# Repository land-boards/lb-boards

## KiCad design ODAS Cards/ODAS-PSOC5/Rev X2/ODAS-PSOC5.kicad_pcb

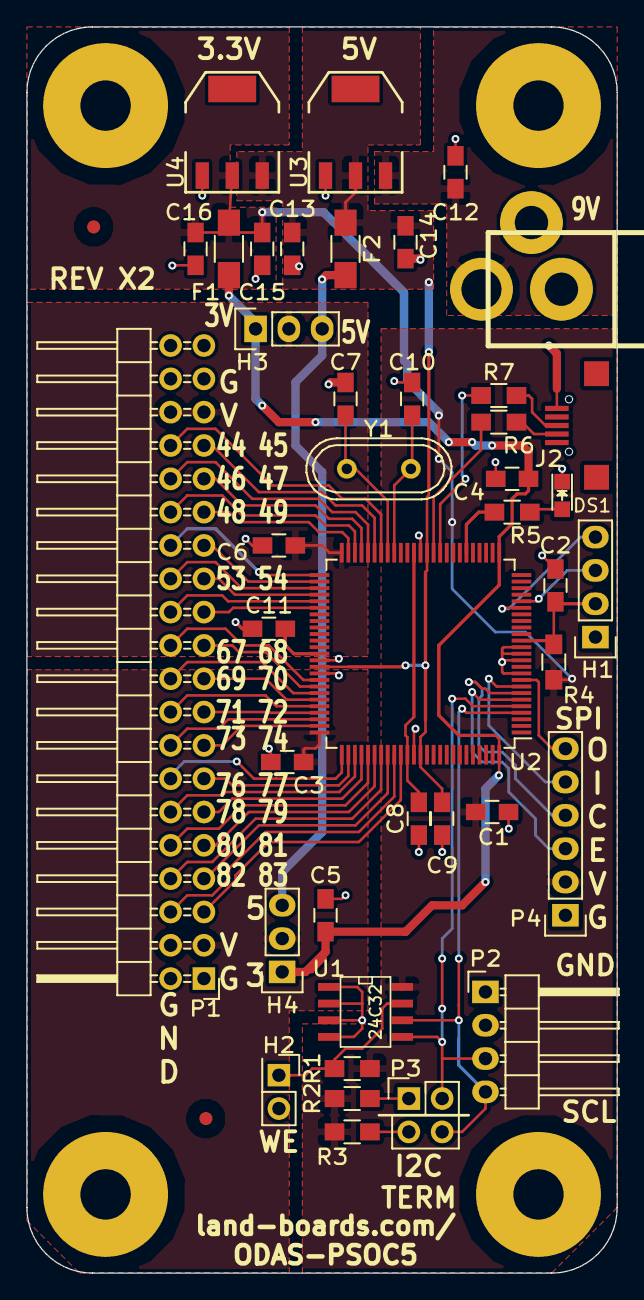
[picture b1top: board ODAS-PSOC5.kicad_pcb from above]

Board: 2 copper layers, 45.0 x 95.0 mm, 48 parts (1 on the bottom side), 60 nets.

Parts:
C1, C2, C3, C4, C5, C6, C9, C12, C13, C14, C15, C16: 0.1uF; C_0805_HandSoldering
C7, C10: C; C_0805_HandSoldering
C8, C11: 1uF; C_0805_HandSoldering
DS1: LED-fixed; LED_0805
F1, F2: FUSE; R_1206_HandSoldering
FID1, FID2: CONN_1; FIDUCIAL
H1: CONN_01X04; Pin_Header_Straight_1x04
H2: CONN_2; Pin_Header_Straight_2x01
H3, H4: CONN_01X03; Pin_Header_Straight_1x03
J1: DCJ0202; JACK_3.5MM
J2: USB-MICRO-B; USB_Micro-B-Wellco-SMT
MTG1, MTG2, MTG3, MTG4: CONN_1; MTG-6-32
P1: CONN_01X40; Pin_Header_Angled_2x20
P2: CONN_01X04; Pin_Header_Angled_1x04
P3: CONN_02X02; Pin_Header_Straight_2x02
P4: CONN_01X06; Pin_Header_Straight_1x06
R1: 1K; R_0805_HandSoldering
R2, R3, R4: 3.9K; R_0805_HandSoldering
R5: 120; R_0805_HandSoldering
R6, R7: 22; R_0805_HandSoldering
TEST: COUPON; REV_BLOCK
U1: 24C32; SO8E-wider
U2: CY8C5267AXI-LP051; TQFP-100_14x14mm_Pitch0.5mm
U3, U4: AP1117; SOT223
Y1: Crystal_Small; Crystal_HC49-U_Vertical

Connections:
+3.3VP: C4.1, C5.1, F1.1, H3.1, H4.1, U2.26, U2.100
+3V3: C1.1, C15.1, C16.1, F1.2, P2.2, P4.2, R1.1, R2.2, R3.2, R4.2, U1.8, U4.2
+5V: C9.2, C13.1, C14.1, F2.2, U2.37, U2.65, U2.88, U3.2, U4.3
+5VP: F2.1, H3.3, H4.3
/+9V: C12.1, J1.1, U3.3
/IO_22: C2.1, H1.2, R4.1, U2.15
/IO_23: H1.3, U2.21
/IO_24: H1.4, U2.20
/P5-4: R5.1, U2.31
/P44: P1.34, U2.44
/P45: P1.33, U2.45
/P46: P1.32, U2.46
/P47: P1.31, U2.47
/P48: P1.30, U2.48
/P49: P1.29, U2.49
/P51: P1.28, U2.51
/P52: P1.27, U2.52
/P53: P1.26, U2.53
/P54: P1.25, U2.54
/P55: P1.24, U2.55
/P56: P1.23, U2.56
/P67: P1.22, U2.67
/P68: P1.21, U2.68
/P69: P1.20, U2.69
/P70: P1.19, U2.70
/P71: P1.18, U2.71
/P72: P1.17, U2.72
/P73: P1.16, U2.73
/P74: P1.15, U2.74
/P76: P1.14, U2.76
/P77: P1.13, U2.77
/P78: P1.12, U2.78
/P79: P1.11, U2.79
/P80: P1.10, U2.80
/P81: P1.9, U2.81
/P82: P1.8, U2.82
/P83: P1.7, U2.83
/P84: P1.6, U2.84
/P85: P1.5, U2.85
/SCL: P2.4, P3.4, U1.6, U2.4
/SDA: P2.3, P3.2, U1.5, U2.5
/SPICE0: P4.3, U2.6
/SPIMISO: P4.5, U2.8
/SPIMOSI: P4.6, U2.9
/SPISCK: P4.4, U2.7
/USB-DM: J2.2, R6.1
/USB-DP: J2.3, R7.1
/VZ0: C3.1, H4.2, P1.3, P1.4, U2.75
/VZ3: C6.1, H3.2, P1.35, P1.36, U2.50
/WR: H2.1, R1.2, U1.7
GND: C1.2, C2.2, C3.2, C4.2, C5.2, C6.2, C7.1, C8.1, C9.1, C10.1, C11.1, C12.2, C13.2, C14.2, C15.2, C16.2, DS1.1, H1.1, H2.2, J1.2, J1.3, J2.5, P1.1, P1.2, P1.37, P1.38, P2.1, P4.1, U1.1, U1.2, U1.3, U1.4, U2.10, U2.12, U2.13, U2.14, U2.38, U2.64, U2.66, U2.87, U3.1, U4.1
unnamed: C7.2, U2.43, Y1.1
unnamed: C8.2, U2.39, U2.86
unnamed: C10.2, U2.42, Y1.2
unnamed: C11.2, U2.63
unnamed: DS1.2, R5.2
unnamed: P3.1, R2.1
unnamed: P3.3, R3.1
unnamed: R6.2, U2.36
unnamed: R7.2, U2.35

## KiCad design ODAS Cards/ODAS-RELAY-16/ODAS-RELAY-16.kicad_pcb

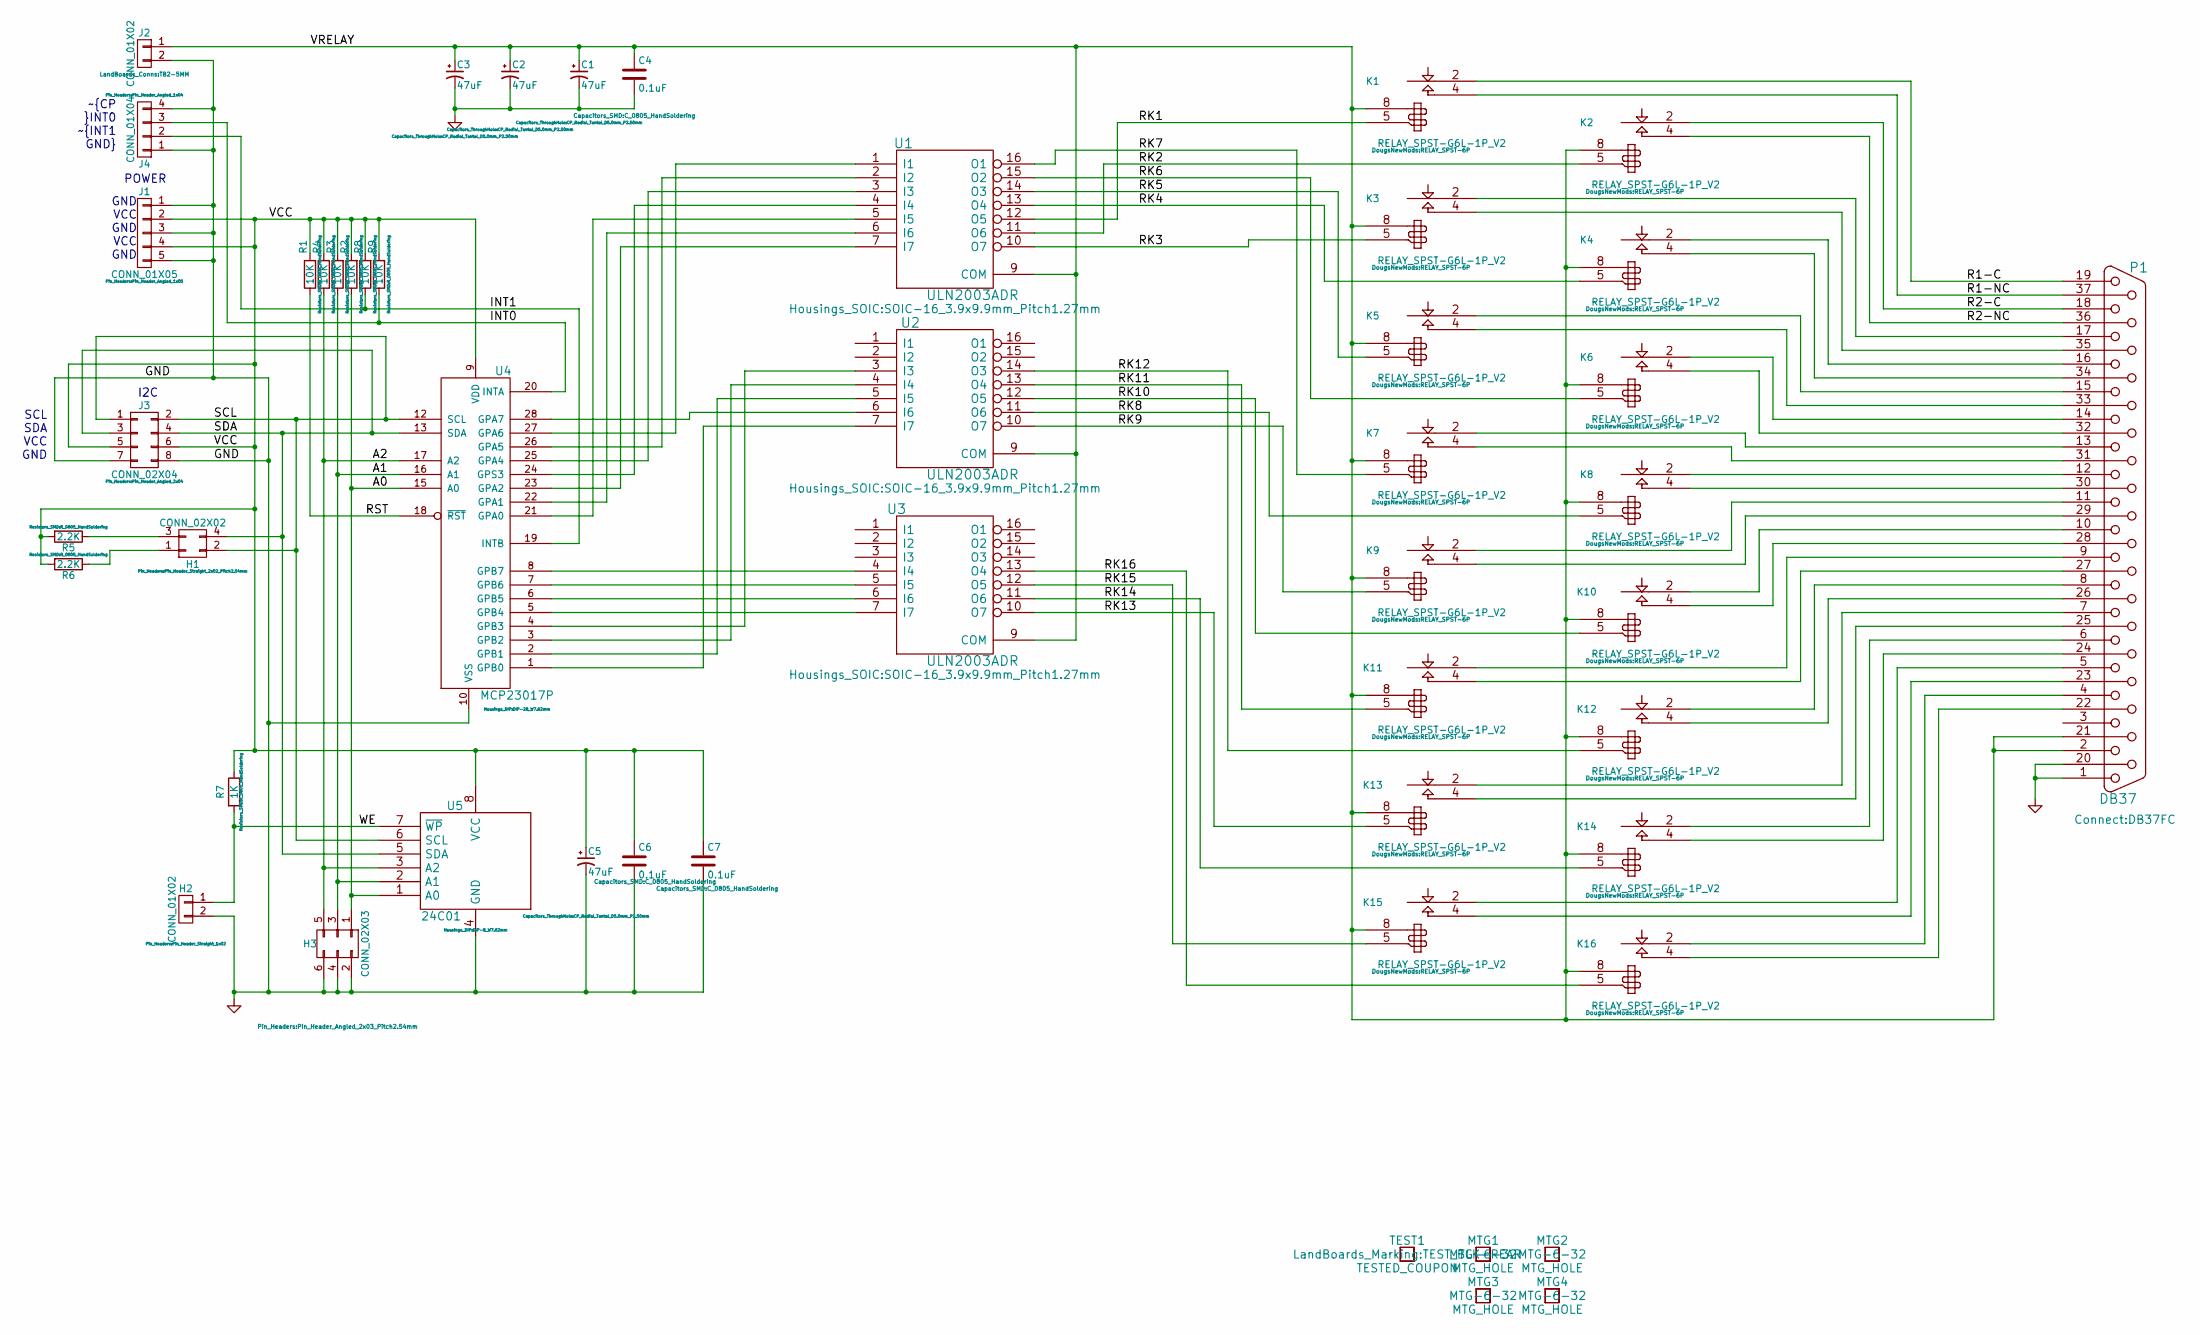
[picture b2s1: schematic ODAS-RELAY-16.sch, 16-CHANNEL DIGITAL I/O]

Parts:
C1, C2, C3, C5: 47uF; CP_Radial_Tantal_D5.0mm_P2.50mm
C4, C6, C7: 0.1uF; C_0805_HandSoldering
H1: CONN_02X02; Pin_Header_Straight_2x02_Pitch2.54mm
H2: CONN_01X02; Pin_Header_Straight_1x02
H3: CONN_02X03; Pin_Header_Angled_2x03_Pitch2.54mm
J1: CONN_01X05; Pin_Header_Angled_1x05
J2: CONN_01X02; TB2-5MM
J3: CONN_02X04; Pin_Header_Angled_2x04
J4: CONN_01X04; Pin_Header_Angled_1x04
K1, K2, K3, K4, K5, K6, K7, K8, K9, K10, K11, K12, K13, K14, K15, K16: RELAY_SPST-G6L-1P_V2; RELAY_SPST-6P
MTG1, MTG2, MTG3, MTG4: MTG_HOLE; MTG-6-32
P1: DB37; DB37FC
R1, R2, R3, R4, R8, R9: 10K; R_0805_HandSoldering
R5, R6: 2.2K; R_0805_HandSoldering
R7: 1K; R_0805_HandSoldering
TEST1: TESTED_COUPON; TEST_BLK-REAR
U1, U2, U3: ULN2003ADR; SOIC-16_3.9x9.9mm_Pitch1.27mm
U4: MCP23017P; DIP-28_W7.62mm
U5: 24C01; DIP-8_W7.62mm

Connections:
/A0: H3.1, R2.1, U4.15 (A0), U5.1 (A0)
/A1: H3.3, R3.1, U4.16 (A1), U5.2 (A1)
/A2: H3.5, R4.1, U4.17 (A2), U5.3 (A2)
/INT0: J4.3, R9.1, U4.20 (INTA)
/INT1: J4.2, R8.1, U4.19 (INTB)
/R1-C: K1.2 (C1), P1.19
/R1-NC: K1.4 (T1), P1.37
/R2-C: K2.2 (C1), P1.18
/R2-NC: K2.4 (T1), P1.36
/RK1: K1.5, U1.12 (O5)
/RK2: K2.5, U1.11 (O6)
/RK3: K3.5, U1.10 (O7)
/RK4: K4.5, U1.13 (O4)
/RK5: K5.5, U1.14 (O3)
/RK6: K6.5, U1.15 (O2)
/RK7: K7.5, U1.16 (O1)
/RK8: K8.5, U2.11 (O6)
/RK9: K9.5, U2.10 (O7)
/RK10: K10.5, U2.12 (O5)
/RK11: K11.5, U2.13 (O4)
/RK12: K12.5, U2.14 (O3)
/RK13: K13.5, U3.10 (O7)
/RK14: K14.5, U3.11 (O6)
/RK15: K15.5, U3.12 (O5)
/RK16: K16.5, U3.13 (O4)
/RST: R1.1, U4.18 (~RST)
/SCL: H1.2, J3.1, J3.2, U4.12 (SCL), U5.6 (SCL)
/SDA: H1.4, J3.3, J3.4, U4.13 (SDA), U5.5 (SDA)
/VCC: C5.1, C6.1, C7.1, J1.2, J1.4, J3.5, J3.6, R1.2, R2.2, R3.2, R4.2, R5.2, R6.2, R7.1, R8.2, R9.2, U4.9 (VDD), U5.8 (VCC)
/VRELAY: C1.1, C2.1, C3.1, C4.1, J2.1, K1.8, K2.8, K3.8, K4.8, K5.8, K6.8, K7.8, K8.8, K9.8, K10.8, K11.8, K12.8, K13.8, K14.8, K15.8, K16.8, P1.2, P1.21, U1.9 (COM), U2.9 (COM), U3.9 (COM)
/WE: H2.1, R7.2, U5.7 (~WP)
GND: C1.2, C2.2, C3.2, C4.2, C5.2, C6.2, C7.2, H2.2, H3.2, H3.4, H3.6, J1.1, J1.3, J1.5, J2.2, J3.7, J3.8, J4.1, J4.4, P1.1, P1.20, U1.8 (GND), U2.8 (GND), U3.8 (GND), U4.10 (VSS), U5.4 (GND)
unnamed: H1.1, R6.1
unnamed: H1.3, R5.1
unnamed: K3.2 (C1), P1.17
unnamed: K3.4 (T1), P1.35
unnamed: K4.2 (C1), P1.16
unnamed: K4.4 (T1), P1.34
unnamed: K5.2 (C1), P1.15
unnamed: K5.4 (T1), P1.33
unnamed: K6.2 (C1), P1.14
unnamed: K6.4 (T1), P1.32
unnamed: K7.2 (C1), P1.13
unnamed: K7.4 (T1), P1.31
unnamed: K8.2 (C1), P1.12
unnamed: K8.4 (T1), P1.30
unnamed: K9.2 (C1), P1.11
unnamed: K9.4 (T1), P1.29
unnamed: K10.2 (C1), P1.10
unnamed: K10.4 (T1), P1.28
unnamed: K11.2 (C1), P1.9
unnamed: K11.4 (T1), P1.27
unnamed: K12.2 (C1), P1.8
unnamed: K12.4 (T1), P1.26
unnamed: K13.2 (C1), P1.7
unnamed: K13.4 (T1), P1.25
unnamed: K14.2 (C1), P1.6
unnamed: K14.4 (T1), P1.24
unnamed: K15.2 (C1), P1.5
unnamed: K15.4 (T1), P1.23
unnamed: K16.2 (C1), P1.4
unnamed: K16.4 (T1), P1.22
unnamed: U1.1 (I1), U4.27 (GPA6)
unnamed: U1.2 (I2), U4.26 (GPA5)
unnamed: U1.3 (I3), U4.25 (GPA4)
unnamed: U1.4 (I4), U4.24 (GPS3)
unnamed: U1.5 (I5), U4.21 (GPA0)
unnamed: U1.6 (I6), U4.22 (GPA1)
unnamed: U1.7 (I7), U4.23 (GPA2)
unnamed: U2.3 (I3), U4.4 (GPB3)
unnamed: U2.4 (I4), U4.3 (GPB2)
unnamed: U2.5 (I5), U4.2 (GPB1)
unnamed: U2.6 (I6), U4.28 (GPA7)
unnamed: U2.7 (I7), U4.1 (GPB0)
unnamed: U3.4 (I4), U4.8 (GPB7)
unnamed: U3.5 (I5), U4.7 (GPB6)
unnamed: U3.6 (I6), U4.6 (GPB5)
unnamed: U3.7 (I7), U4.5 (GPB4)

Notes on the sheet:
SCL SDA VCC GND
GND VCC GND VCC GND
~CP ~INT0 ~INT1 GND
POWER
I2C

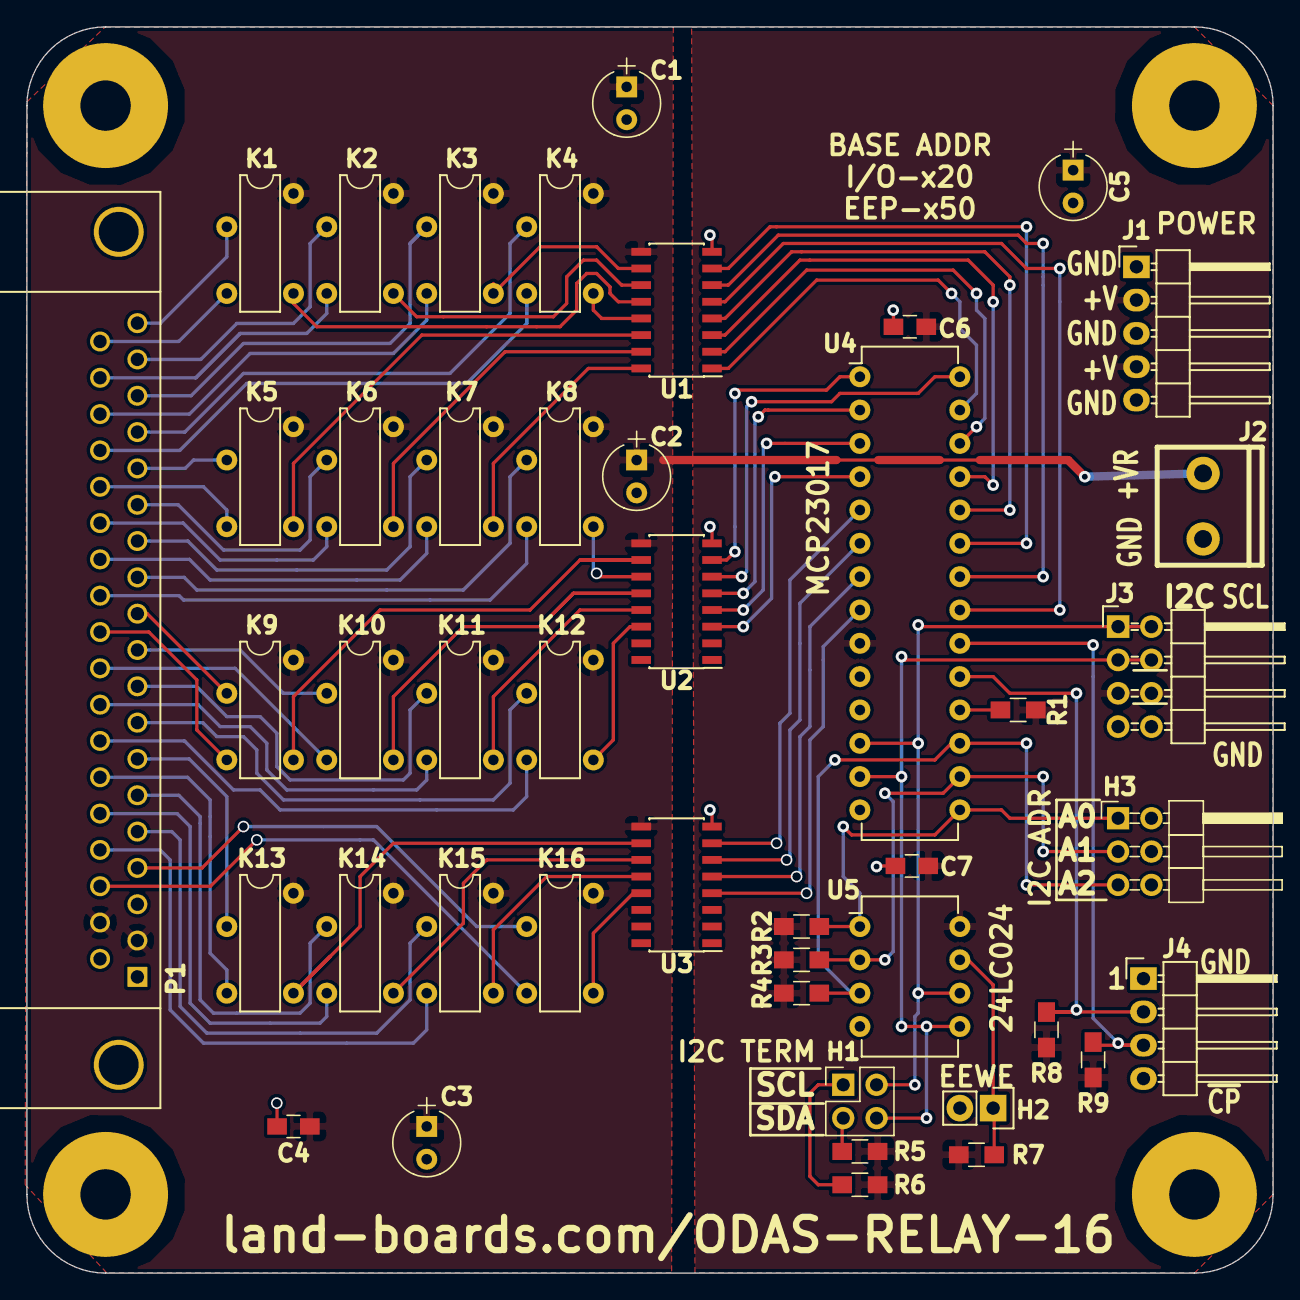
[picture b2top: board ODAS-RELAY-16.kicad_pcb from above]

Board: 2 copper layers, 95.0 x 95.0 mm, 50 parts (0 on the bottom side), 78 nets.

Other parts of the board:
TEST: TESTED_COUPON; TEST_BLK-REAR

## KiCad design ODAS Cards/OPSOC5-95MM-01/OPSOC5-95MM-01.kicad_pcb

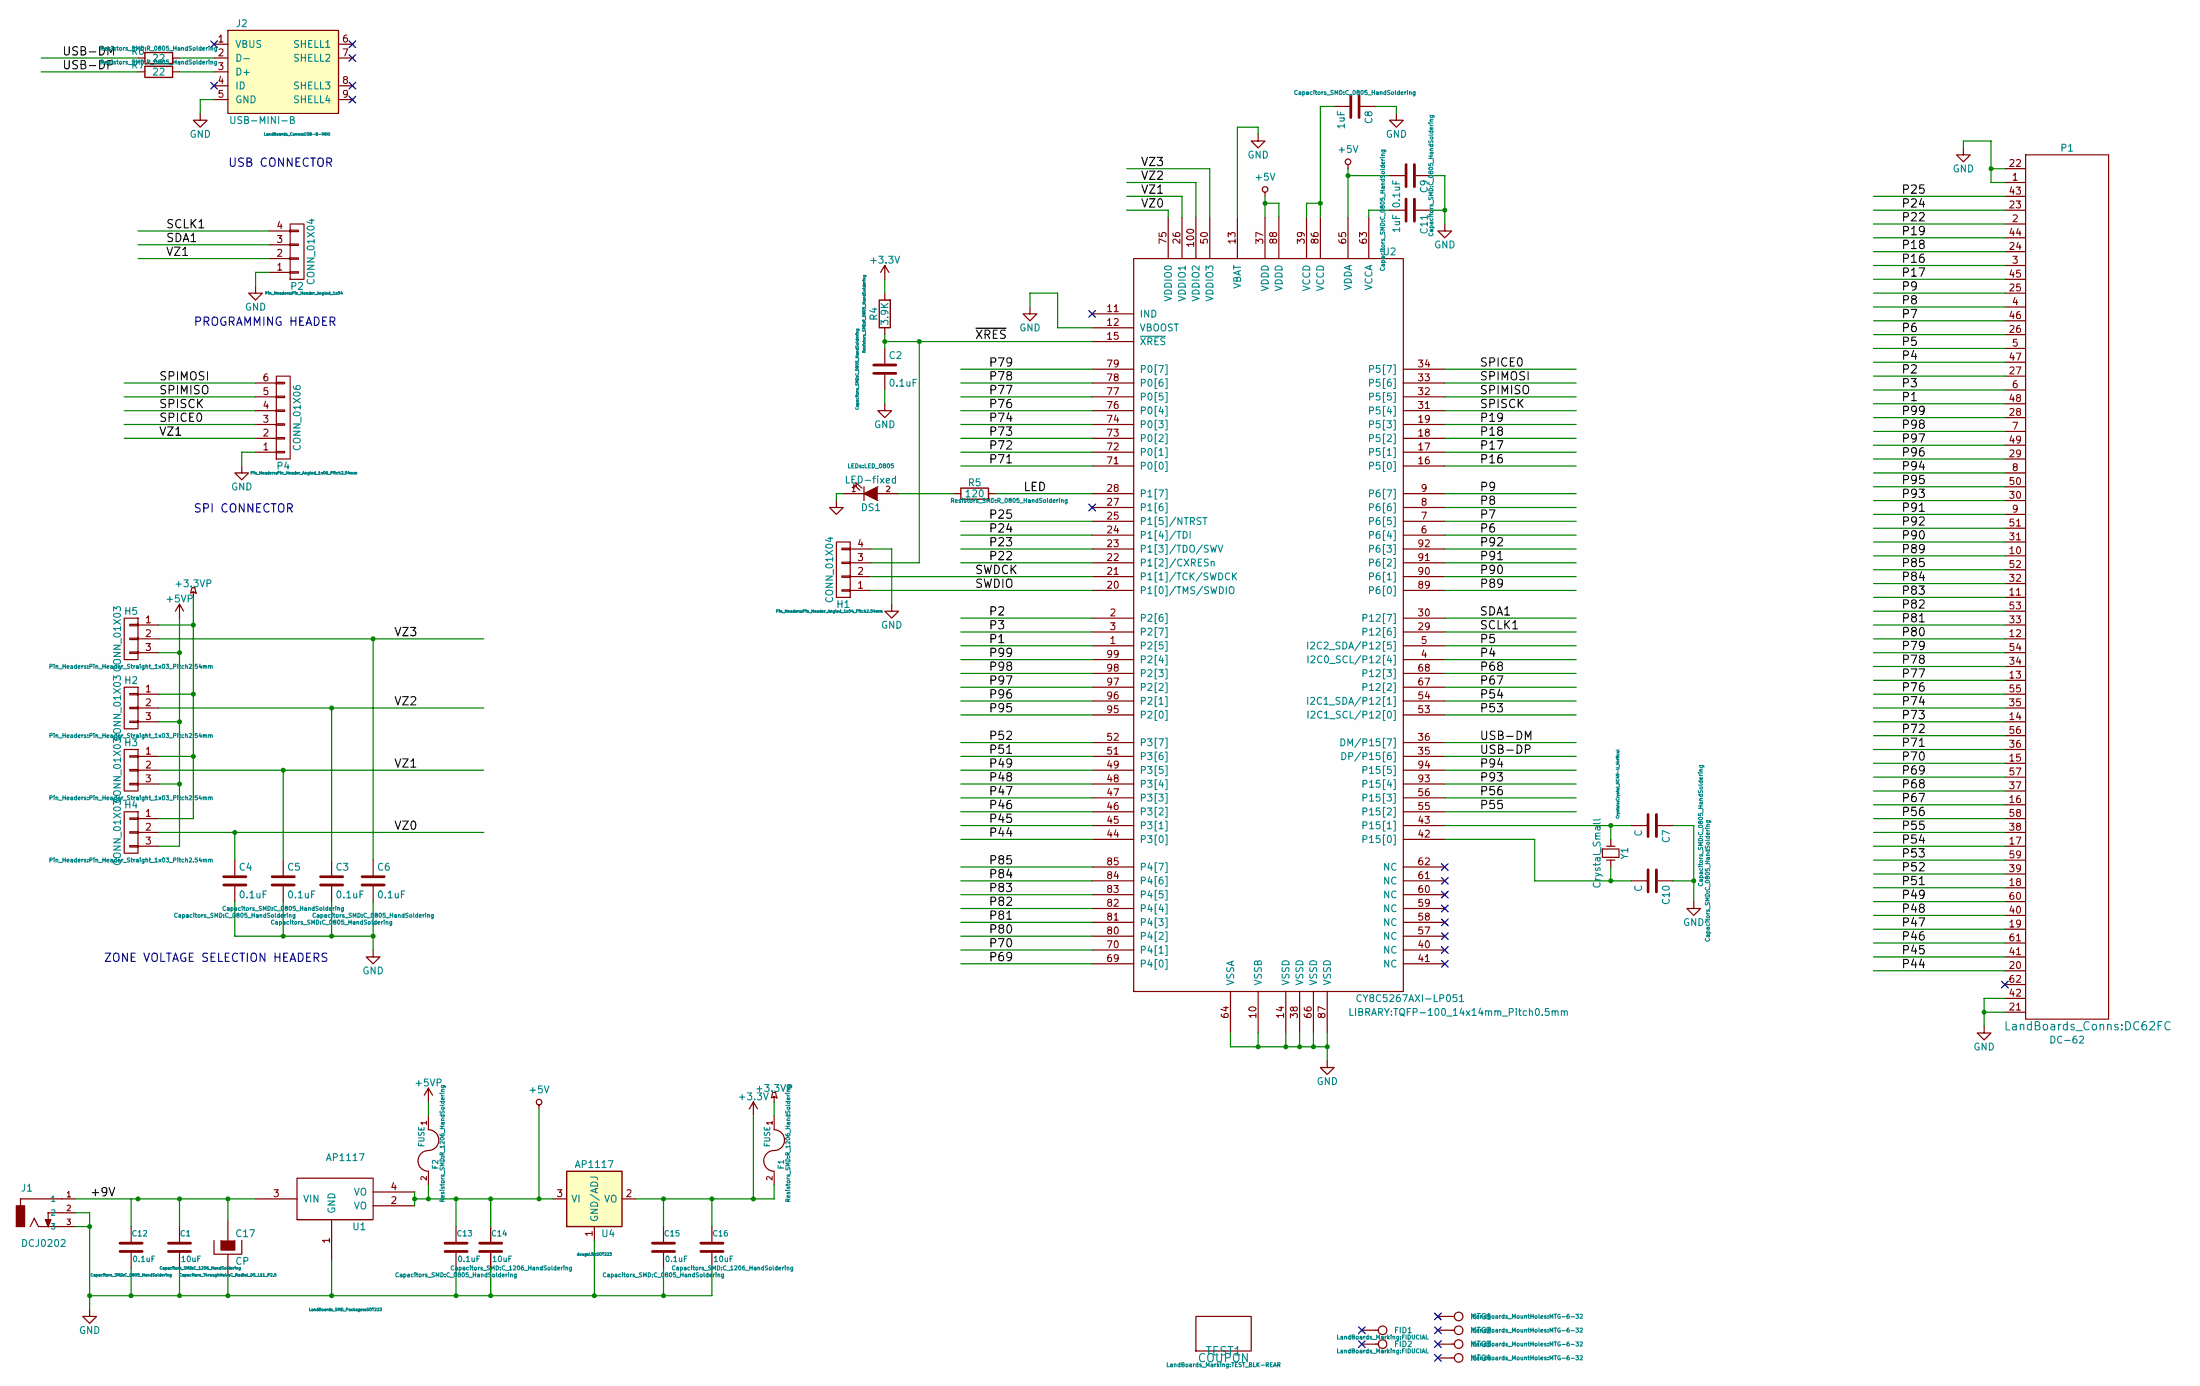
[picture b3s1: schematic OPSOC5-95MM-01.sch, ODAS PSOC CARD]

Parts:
C1, C14, C16: 10uF; C_1206_HandSoldering
C2, C3, C4, C5, C6, C9, C12, C13, C15: 0.1uF; C_0805_HandSoldering
C7, C10: C; C_0805_HandSoldering
C8, C11: 1uF; C_0805_HandSoldering
C17: CP; C_Radial_D5_L11_P2.5
DS1: LED-fixed; LED_0805
F1, F2: FUSE; R_1206_HandSoldering
FID1, FID2: CONN_1; FIDUCIAL
H1: CONN_01X04; Pin_Header_Angled_1x04_Pitch2.54mm
H2, H3, H4, H5: CONN_01X03; Pin_Header_Straight_1x03_Pitch2.54mm
J1: DCJ0202; JACK_3.5MM
J2: USB-MINI-B; USB-B-MINI
MTG1, MTG2, MTG3, MTG4: CONN_1; MTG-6-32
P1: DC-62; DC62FC
P2: CONN_01X04; Pin_Header_Angled_1x04
P4: CONN_01X06; Pin_Header_Angled_1x06_Pitch2.54mm
R4: 3.9K; R_0805_HandSoldering
R5: 120; R_0805_HandSoldering
R6, R7: 22; R_0805_HandSoldering
TEST1: COUPON; TEST_BLK-REAR
U1, U4: AP1117; SOT223
U2: CY8C5267AXI-LP051; TQFP-100_14x14mm_Pitch0.5mm
Y1: Crystal_Small; Crystal_HC49-U_Vertical

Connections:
+3.3VP: F1.1, H2.1, H3.1, H4.1, H5.1
+3V3: C15.1, C16.1, F1.2, R4.2, U4.2 (VO)
+5V: C9.2, C13.1, C14.1, F2.2, U1.2 (VO), U1.4 (VO), U2.37 (VDDD), U2.65 (VDDA), U2.88 (VDDD), U4.3 (VI)
+5VP: F2.1, H2.3, H3.3, H4.3, H5.3
/+9V: C1.1, C17.1, J1.1, U1.3 (VIN)
/LED: R5.2, U2.28 (P1[7])
/P1: P1.48, U2.1 (P2[5])
/P2: P1.27, U2.2 (P2[6])
/P3: P1.6, U2.3 (P2[7])
/P4: P1.47, U2.4 (I2C0_SCL/P12[4])
/P5: P1.5, U2.5 (I2C2_SDA/P12[5])
/P6: P1.26, U2.6 (P6[4])
/P7: P1.46, U2.7 (P6[5])
/P8: P1.4, U2.8 (P6[6])
/P9: P1.25, U2.9 (P6[7])
/P16: P1.3, U2.16 (P5[0])
/P17: P1.45, U2.17 (P5[1])
/P18: P1.24, U2.18 (P5[2])
/P19: P1.44, U2.19 (P5[3])
/P22: P1.2, U2.22 (P1[2]/CXRESn)
/P24: P1.23, U2.24 (P1[4]/TDI)
/P25: P1.43, U2.25 (P1[5]/NTRST)
/P44: P1.20, U2.44 (P3[0])
/P45: P1.41, U2.45 (P3[1])
/P46: P1.61, U2.46 (P3[2])
/P47: P1.19, U2.47 (P3[3])
/P48: P1.40, U2.48 (P3[4])
/P49: P1.60, U2.49 (P3[5])
/P51: P1.18, U2.51 (P3[6])
/P52: P1.39, U2.52 (P3[7])
/P53: P1.59, U2.53 (I2C1_SCL/P12[0])
/P54: P1.17, U2.54 (I2C1_SDA/P12[1])
/P55: P1.38, U2.55 (P15[2])
/P56: P1.58, U2.56 (P15[3])
/P67: P1.16, U2.67 (P12[2])
/P68: P1.37, U2.68 (P12[3])
/P69: P1.57, U2.69 (P4[0])
/P70: P1.15, U2.70 (P4[1])
/P71: P1.36, U2.71 (P0[0])
/P72: P1.56, U2.72 (P0[1])
/P73: P1.14, U2.73 (P0[2])
/P74: P1.35, U2.74 (P0[3])
/P76: P1.55, U2.76 (P0[4])
/P77: P1.13, U2.77 (P0[5])
/P78: P1.34, U2.78 (P0[6])
/P79: P1.54, U2.79 (P0[7])
/P80: P1.12, U2.80 (P4[2])
/P81: P1.33, U2.81 (P4[3])
/P82: P1.53, U2.82 (P4[4])
/P83: P1.11, U2.83 (P4[5])
/P84: P1.32, U2.84 (P4[6])
/P85: P1.52, U2.85 (P4[7])
/P89: P1.10, U2.89 (P6[0])
/P90: P1.31, U2.90 (P6[1])
/P91: P1.9, U2.91 (P6[2])
/P92: P1.51, U2.92 (P6[3])
/P93: P1.30, U2.93 (P15[4])
/P94: P1.8, U2.94 (P15[5])
/P95: P1.50, U2.95 (P2[0])
/P96: P1.29, U2.96 (P2[1])
/P97: P1.49, U2.97 (P2[2])
/P98: P1.7, U2.98 (P2[3])
/P99: P1.28, U2.99 (P2[4])
/SCLK1: P2.4, U2.29 (P12[6])
/SDA1: P2.3, U2.30 (P12[7])
/SPICE0: P4.3, U2.34 (P5[7])
/SPIMISO: P4.5, U2.32 (P5[5])
/SPIMOSI: P4.6, U2.33 (P5[6])
/SPISCK: P4.4, U2.31 (P5[4])
/SWDCK: H1.2, U2.21 (P1[1]/TCK/SWDCK)
/SWDIO: H1.1, U2.20 (P1[0]/TMS/SWDIO)
/USB-DM: R6.2, U2.36 (DM/P15[7])
/USB-DP: R7.2, U2.35 (DP/P15[6])
/VZ0: C4.1, H4.2, U2.75 (VDDIO0)
/VZ1: C5.1, H3.2, P2.2, P4.2, U2.26 (VDDIO1)
/VZ2: C3.1, H2.2, U2.100 (VDDIO2)
/VZ3: C6.1, H5.2, U2.50 (VDDIO3)
/~XRES: C2.1, H1.3, R4.1, U2.15 (~XRES)
GND: C1.2, C2.2, C3.2, C4.2, C5.2, C6.2, C7.1, C8.1, C9.1, C10.1, C11.1, C12.2, C13.2, C14.2, C15.2, C16.2, C17.2, DS1.1 (K), H1.4, J1.2, J1.3, J2.5 (GND), P1.1, P1.21, P1.22, P1.42, P2.1, P4.1, U1.1 (GND), U2.10 (VSSB), U2.12 (VBOOST), U2.13 (VBAT), U2.14 (VSSD), U2.38 (VSSD), U2.64 (VSSA), U2.66 (VSSD), U2.87 (VSSD), U4.1 (GND/ADJ)
unnamed: C7.2, U2.43 (P15[1]), Y1.1
unnamed: C8.2, U2.39 (VCCD), U2.86 (VCCD)
unnamed: C10.2, U2.42 (P15[0]), Y1.2
unnamed: C11.2, U2.63 (VCCA)
unnamed: DS1.2 (A), R5.1
unnamed: J2.2 (D-), R6.1
unnamed: J2.3 (D+), R7.1

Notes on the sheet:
PROGRAMMING HEADER
USB CONNECTOR
SPI CONNECTOR
ZONE VOLTAGE SELECTION HEADERS

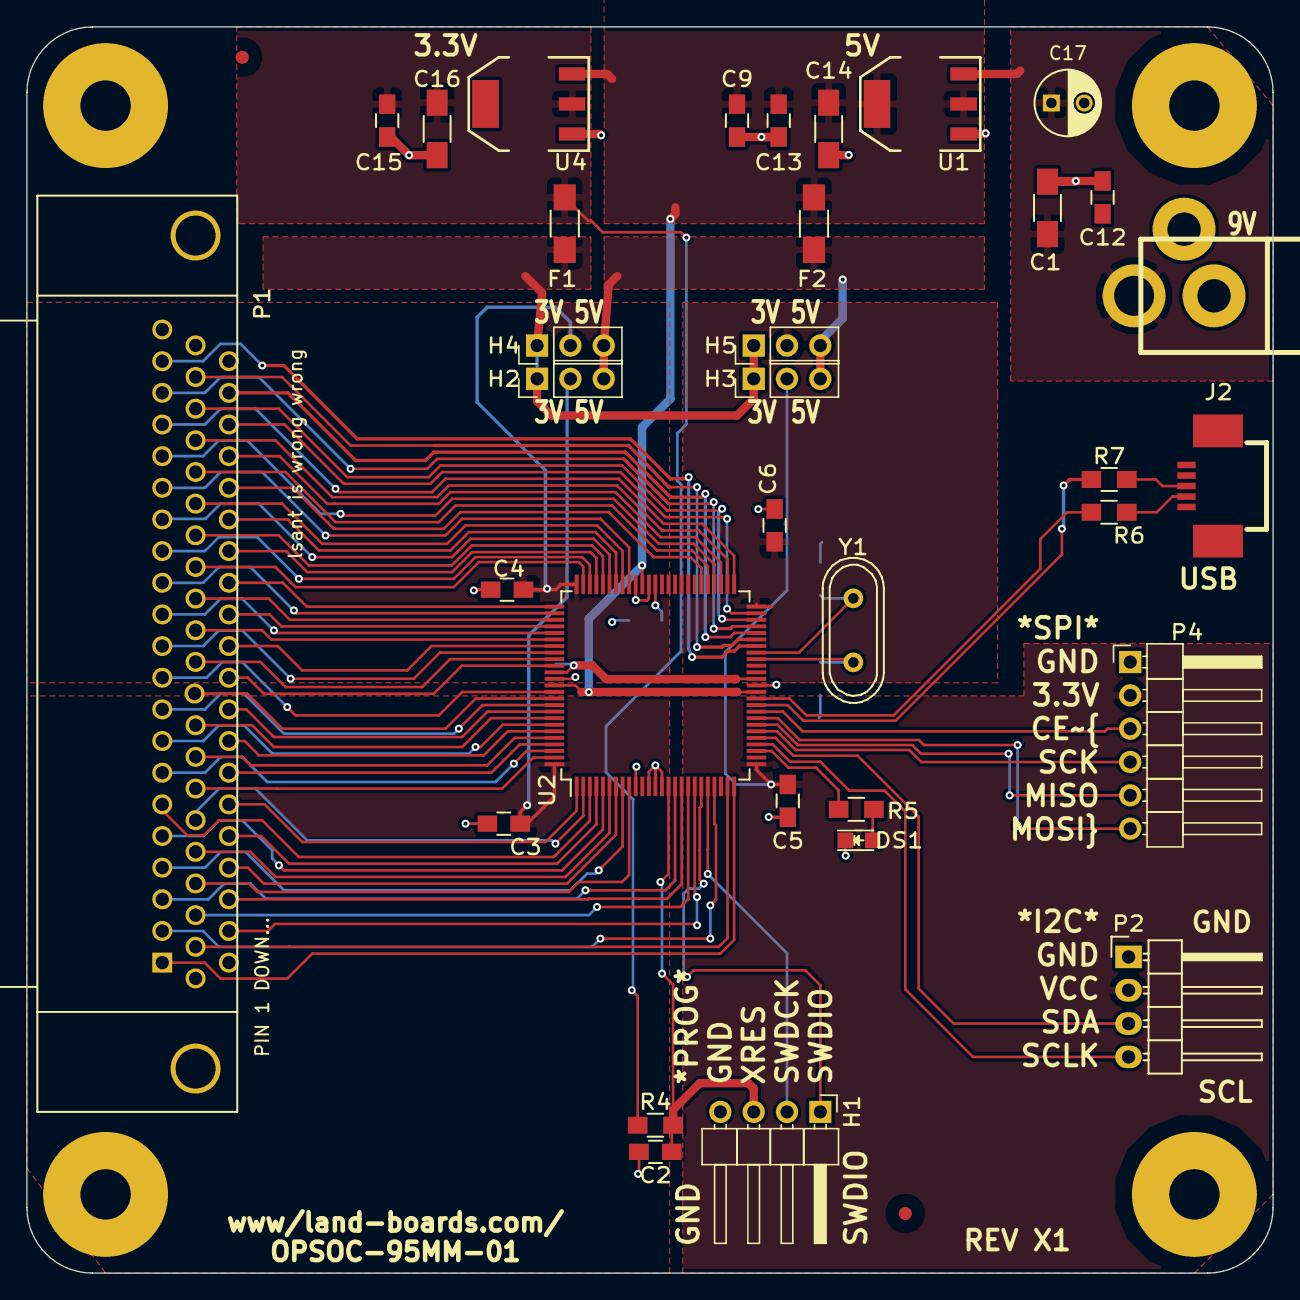
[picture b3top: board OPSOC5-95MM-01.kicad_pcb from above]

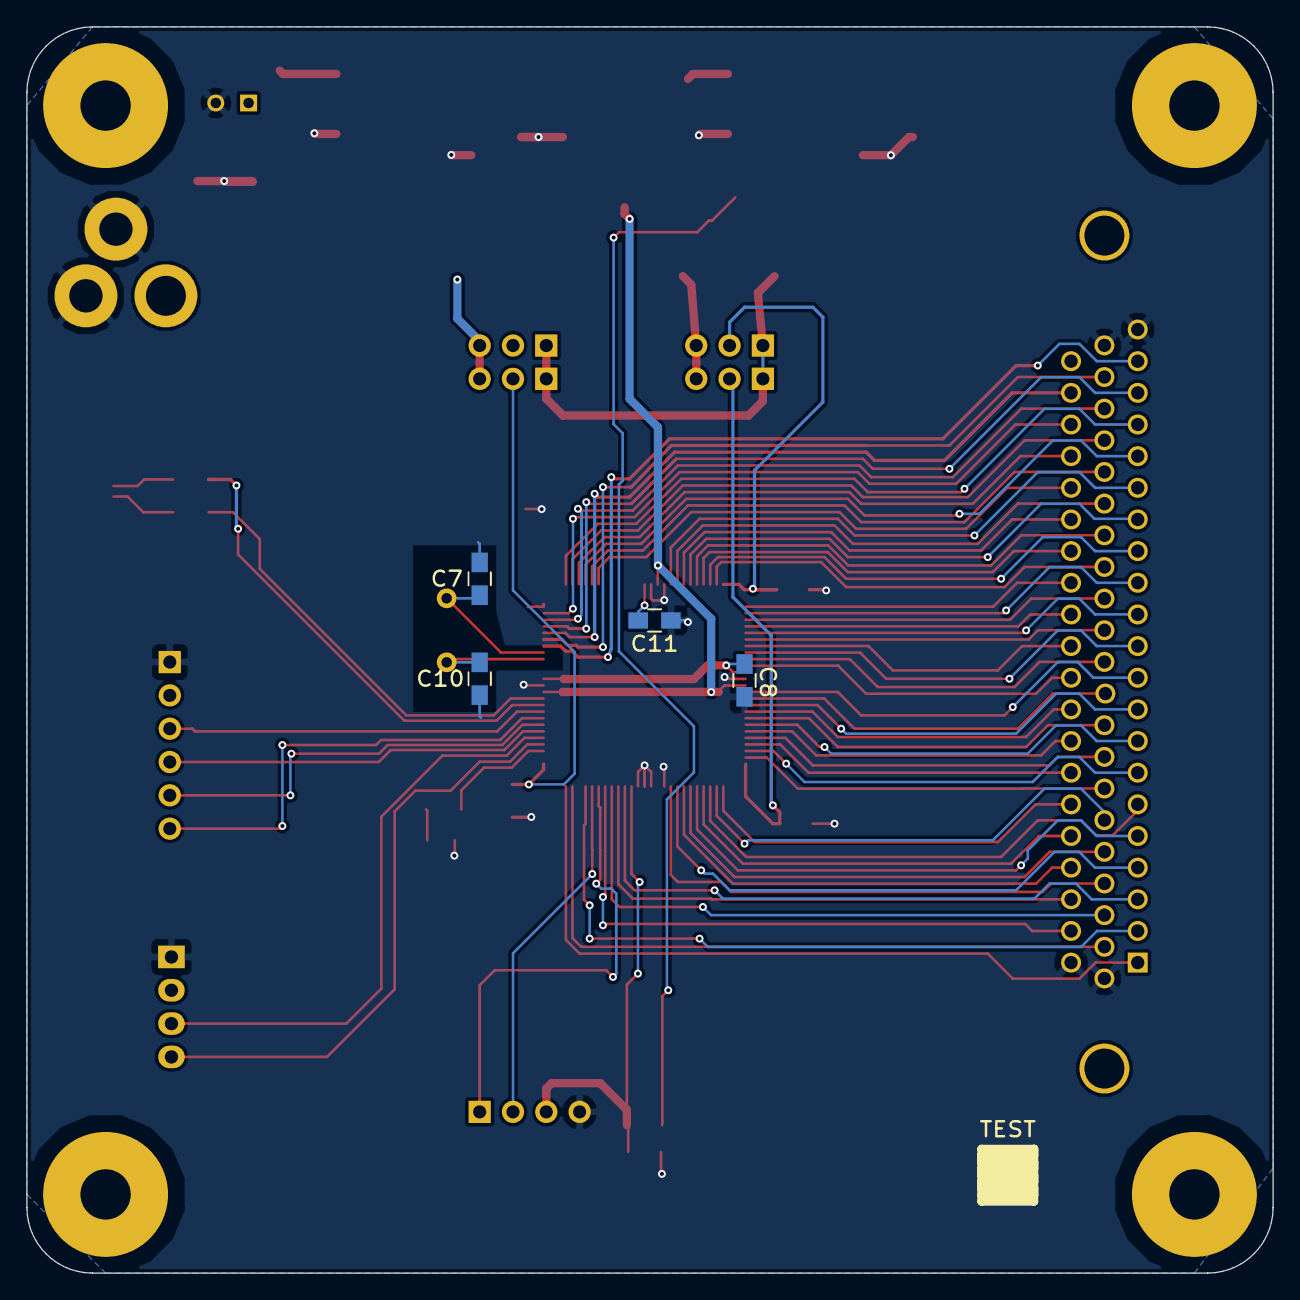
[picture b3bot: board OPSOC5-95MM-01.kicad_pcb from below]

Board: 2 copper layers, 95.0 x 95.0 mm, 45 parts (4 on the bottom side), 86 nets.

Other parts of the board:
TEST: COUPON; TEST_BLK-REAR

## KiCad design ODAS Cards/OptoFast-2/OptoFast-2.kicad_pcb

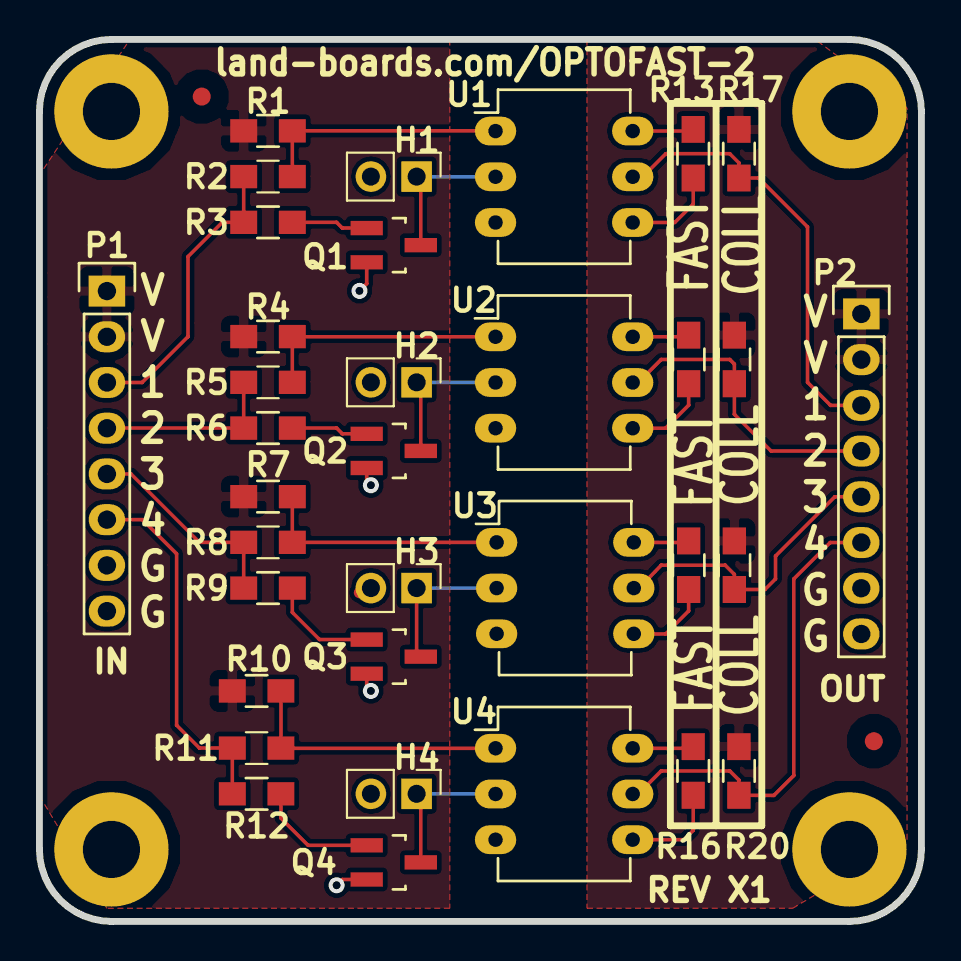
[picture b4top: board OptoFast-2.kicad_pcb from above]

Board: 2 copper layers, 49.0 x 49.0 mm, 41 parts (0 on the bottom side), 28 nets.

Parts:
FID1, FID2: ADAFRUIT_FIDUCIAL; FIDUCIAL
H1, H2, H3, H4: DNP; Pin_Header_Straight_1x02_Pitch2.54mm
MTG1, MTG2, MTG3, MTG4: MTG_HOLE; MTG-4-40
P1, P2: CONN_01X08; Pin_Header_Straight_1x08
Q1, Q2, Q3, Q4: 2N3904; SOT-23_Handsoldering
R1, R4, R7, R10: 150; R_0805_HandSoldering
R2, R5, R8, R11: DNP; R_0805_HandSoldering
R3, R6, R9, R12: 10K; R_0805_HandSoldering
R13, R14, R15, R16: 20K; R_0805_HandSoldering
R17, R18, R19, R20: 1.2K; R_0805_HandSoldering
TEST: COUPON; TEST_BLK-REAR
U1, U2, U3, U4: 4N26; DIP-6_W7.62mm_LongPads

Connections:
/OptoBlk1/GND1: H1.2, H2.2, H3.2, H4.2, P1.7, P1.8, Q1.2, Q2.2, Q3.2, Q4.2
/OptoBlk1/GND2: P2.7, P2.8, R13.2, R14.2, R15.2, R16.2, U1.4, U2.4, U3.4, U4.4
/OptoBlk1/IN1: P1.3, R2.1, R3.1
/OptoBlk1/OUT: P2.3, R17.1, U1.5
/OptoBlk1/VCC1: P1.1, P1.2, R1.1, R4.1, R7.1, R10.1
/OptoBlk1/VCC2: P2.1, P2.2, R17.2, R18.2, R19.2, R20.2
/OptoBlk2/IN1: P1.4, R5.1, R6.1
/OptoBlk2/OUT: P2.4, R18.1, U2.5
/OptoBlk3/IN1: P1.5, R8.1, R9.1
/OptoBlk3/OUT: P2.5, R19.1, U3.5
/OptoBlk4/IN1: P1.6, R11.1, R12.1
/OptoBlk4/OUT: P2.6, R20.1, U4.5
unnamed: H1.1, Q1.3, U1.2
unnamed: H2.1, Q2.3, U2.2
unnamed: H3.1, Q3.3, U3.2
unnamed: H4.1, Q4.3, U4.2
unnamed: Q1.1, R3.2
unnamed: Q2.1, R6.2
unnamed: Q3.1, R9.2
unnamed: Q4.1, R12.2
unnamed: R1.2, R2.2, U1.1
unnamed: R4.2, R5.2, U2.1
unnamed: R7.2, R8.2, U3.1
unnamed: R10.2, R11.2, U4.1
unnamed: R13.1, U1.6
unnamed: R14.1, U2.6
unnamed: R15.1, U3.6
unnamed: R16.1, U4.6
